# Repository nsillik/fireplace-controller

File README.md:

# Nick's Fireplace Controller Thingy

## Why did you make this?

In 2022 we bought an _old_ house. A big ol' victorian built in 1891 which had been converted to a triplex. Unfortunately during this conversion they ripped out all 8 or so original fireplaces an bricked them up. Lame. So, we though we'd put in some gas fireplaces. We did! Then we needed a way to control them, so we bought this amazing remote control system for $500 each:

Yes, that's a resistive touch screen. Yes, it really is that ugly and clunky. Yes it did somehow cost $500 dollars. No, that is not my hand. It also does all sorts of annoying things, like only allow you to adust the time by one minute, so if you want to run your fireplace for 2 hours, have fun hitting the (again, resistive) "add minute" button _one hundred and twenty times_.

I hated this, my wife ([@jensillik](https://github.com/jensillik)) hated it, so we decided to do something about it. And here it is.

## How did you make it?

Well, like every computer person of a certain age, I have a giant pile of electronics, raspberry pis, arduinos, ESP8266s, ESP32s, PICs, PIDs, and whatnot lying around that I always pretended I would do something useful with. Mostly I would make an LED blink every few seconds, or say "I'm going to build a robot" and then… make an LED blink every few seconds.

So I gathered up some of my bits and bobs – namely an ESP32, a breadboard, some resistors, a relay, and _of course_ some LEDs for blinking – and slapped them together into some configuration that I was pretty sure would actually control the fireplace's electronics. Then I wrote some firmware code in ESP-IDF that actually turns on and off the relay (_and_ blinks LEDs). I wrote an iOS app (that was ugly), then Jen made some beautiful Figma designs, and so I made the app pretty! Finally I (tried) to build the schematics and PCB layouts for eventual actual-production of hardware!

That all became the following three things:

- *Flicker*: the firmware running on an ESP32 which handles wifi networking, a custom UDP protocol for remote control, and hareware control of the relay for turning the fireplace on and off.

- *Flame*: an iOS app, written in SwiftUI, for the users (all two of us) to control the fireplaces and view their statuses.

- *Spark*: a [KiCad](https://www.kicad.org/) project with schematics, BOM, and PCB layout for eventually actually manufacturing a good looking piece of hardware instead of a breadboard shoved under the fireplace.

Read on for details of all three

### ⚡️ Flicker - ESP32 Firmware

If you're in to electronics projects and somehow haven't heard of the [ESP32](https://www.espressif.com/en/products/socs/esp32), you're missing out. What a cool little chip! It's got:

- A dual core processor!
- 520KB of RAM!
- 448KB of ROM!
- WiFi (802.11 b/g/n)!
- Bluetooth (including BLE)!
- Tons of GPIO, ADCs, DACs, SPI, I2S, I2C, and more!

And it costs something like $6 for a devevelopment board!

For this project it's probably a bit of overkill, of course, since I'm using exactly _one_ GPIO. But the WiFi is _way_ easier – and cheaper – to get up and running than screwing around with an Arduino and some sort of shield. Also I had like 10 of them in a drawer, so why not?

When programming the ESP32 you can either use the Arduino SDK that everyone knows and loves, or Expressif's [ESP-IDF](https://docs.espressif.com/projects/esp-idf/en/latest/esp32/get-started/). I've done a bunch of things (like… making LEDs blink _a lot_) in Arduino, so I decided to use ESP-IDF just for fun.

For development I used [VSCode](https://code.visualstudio.com/) and the [PlatformIO](https://platformio.org/) extension which has boards and extensions and libraries and whatnot for the ESP32.

There's really only three interesting pieces of the code:

- The communcation protocol handler
- The wifi code
- The main app that ties it all together

I won't talk much about the last two, as they're pretty much just copies of the reference implementations for each from Expressif's docs with some things hardcoded for my network, like my WPA2 key (please don't hack me).

The communications handler (in [`/flicker/src/listener.c`](/flicker/src/listener.c)) is fun, and has a good description of the custom protocol in it. Here's how it works:

`udp_server_task` is a function that you pass to [FreeRTOS's](https://www.freertos.org/index.html) [`xTaskCreate`](https://www.freertos.org/a00125.html). This creates a task which FreeRTOS will schedule (somehow! I've not dug too deep into the guts).

This `udp_server_task` then binds a UDP (`SOCK_DGRAM`) listener on port `42069` (sorry, sorry, I'm trying to delete it), and then just busyloops listening for any messages. "Messages" here are just a super-simple protocol:

```
// 
// Command structure:
// Clients send commands in the following format:
// 0000 0000 0000 0000
// ^^|---------------|
// ||        | 
// ||        \--------> For command `10` The amount of time, in seconds to turn on for (for turn on command). Otherwise unused (zero is recommended)
// ||  
// \\-----------------> The command to send `00` for turn off, `01` for status, `10` for turn on
// 
// Server always replies with its status, either:
//  - `0000 0000 0000 0000` for off
//  - `10XX XXXX XXXX XXXX` for on, with the Xs being the time remaining in seconds
```

Basically a client can do three things:
- Send `0x4000`, requesting the status
- Send `0x8000 | (0x3FFF & 0xXXXX)` to turn the fireplace on for `XXXX` seconds (well, with the top two bits masked off)
- Send `0x0000` to turn the fireplace off.

When the server recieves these from the clients it updates it's current status which is just a shared (kinda gross, I know) `uint16_t`, and then sends the current (or updated) status back to the client.

There's another FreeRTOS task in `listener.c` called `statusLoop` which, every second, takes a look at the current status, and makes sure that the hardware is doing the right thing. That is:

- If the current status is `on`, decrement the time remaining by one second, and if it's now zero set the status to `off`.
- If the current status if `on`, and there's time remaining, make sure the `RELAY_PIN` is set to on. This closes the relay and the fireplace turns – or stays – on fire.
- If the current status is `off`, open the relay thereby turning the fireplace off, extinguishing the flame.

That's about it!

You'll see how this is all hooked up in [`flicker/src/main.c`](/flicker/src/main.c), which only does three things:

1. Sets up the networking (lines 12-21)
2. Schedules the two tasks above (lines 22 and 23).

That's it! Now we're ready for a client to actually start talking to it.

### 🔥 Flame - iOS App

And this is that client. An iOS app, written in SwiftUI, designed by the wonderul Jen Sillik. Here's the design:

There's only a few big pieces here:

- A `FireplaceService` which handles communication with the `Flicker` controller, as well as a test version for using in Xcode Previews.
- A `MainScreen` which is 100% of the UI and logic.
- A couple views like the custom `Picker`, the `GlassButtonStyle`, and the pretty `BackgroundView`.

#### `FireplaceService`

The [`FireplaceService`](/flame/flame/Services/FireplaceService.swift) is really the heart of the application. It's a reasonably simple protocol to conform to:

```swift
protocol FireplaceService: ObservableObject {
  var fireplaces: [Fireplace] { get }
  func turnOnFireplace(_ fireplace: Fireplace, minutes: UInt16) async -> Fireplace
  func turnOffFireplace(_ fireplace: Fireplace) async -> Fireplace
}
```

You can get a list of fireplaces. You can turn on the fireplace. You can turn off the fireplace. Not really much else to do! The `LiveFireplaceService` implements the real-for-real version of this which connects to the fireplaces in my house. The IP addresses are hardcoded, since I have my DHCP server always assign the same IP to the devices (because I'm lazy and didn't feel like doing mDNS in ESP-IDF, maybe some day).

Basically when this guy is `init`-ed it connects to all of the hardcoded fireplaces, gets their status, and then sets a timer to check on the status of the fireplaces every 20 seconds (I had it doing it every 200ms, but that was silly!). This is all done using the built in [`NWConnection`](https://developer.apple.com/documentation/network/nwconnection) which is pretty straightforward.

The connecting happens in the `connectTo` function which is pretty boring boilerplate, so I'm not going to say anymore about that.

The `requestStatus(fireplace:, connection:)` method sends the status message (`0x4000`), and that's it. Messages recieved _from_ the `Flicker` controllers are handled by the `receive(fireplace:, connection:)` method, and literally just update our internal list of fireplaces.

The `turnOnFireplace(_ fireplace: Fireplace, minutes: UInt16)` and `turnOffFireplace(_ fireplace:)` methods just send the corresponding commands to the specified `Fireplace`. Easy-peasy.

Alllll of this is then injected into the SwiftUI Environment as an `EnvironmentObject` as a lazy-man's form of dependency injection.

#### `MainScreen`

The [`MainScreen`](/flame/flame/MainScreen.swift) is the only screen in the app (if only every app was just a single screen…), it's got a `FireplaceService` that it gets like so:
```swift
@EnvironmentObject var fireplaceService
```

And it keeps its state updated based on the currently selected fireplace (and that fireplaces current state). And then (depending on the current state), it has buttons to turn on, turn off, and adjust the time of the current selected fireplace.

#### Some rando views

There's a couple views in here too, but they're not to interesting. Quickly:

- [`Picker`](/flame/flame/Views/Picker.swift): is just a custom little picker view to match Jen's designs. You give it `options`, and it has a `@Binding` for the currently selected option. Neato!
- [`GlassButton`](/flame/flame/Views/GlassButton.swift): is a custom `ButtonStyle` for making the glassy looking buttons. There's actually a little bug here, but I haven't got a chance to sit down w/ my fantastic designer to work them out. It's good enough for now!
- [`BackgroundView`](/flame/flame/Views/BackgroundView.swift): is the pretty view that's the background of the whole app. It's a steely blue-gray color when the fireplace is off, and a warm orange-yellow color when the fireplace is on. Eventually I'm going to make this pretty and feel more alive.

#### That's it

Yeah, really. That's the whole app

### ✨ Spark - Hardware Design

As an added challenge I am trying to actually get the hardware manufactured. I haven't done it yet, and it'll probably be a disaster, but you can take a look at my attempts!

I'm using [KiCad](https://www.kicad.org/), a free and open-source EDA tool. To start, I needed to build a schematic. I used the [ESP32-DevKitC V4](https://docs.espressif.com/projects/esp-idf/en/latest/esp32/hw-reference/esp32/get-started-devkitc.html) as my starting guide. This includes:

- The ESP32
- A usb connector
- A [`CP2102N`](https://www.silabs.com/documents/public/data-sheets/cp2102n-datasheet.pdf) USB-to-UART controller for serial access
- An [`AS1117`](http://www.advanced-monolithic.com/pdf/ds1117.pdf) voltage regulator for going from USBs 5v to the 3.3v that the ESP32 runs on.
- A few buttons, transistors, caps, resistors, diodes, and – of course – blinking LEDs.

On top of that I added a [SRD-03VDC-SL-C](https://pdf1.alldatasheet.com/datasheet-pdf/view/1132027/SONGLERELAY/SRD-03VDC-SL-C.html) relay for actually controlling the fireplace. Oh yeah, and there's some transistors and resistors and diodes around the relay so that it… relays correctly? IDK 🤷‍♀️

I laid that all out in the schematic editor – mostly according to datasheets, example circuits, and with the help of a few buddies – and it ended up looking like this:

After that I had to put together the BOM and footprints (although, I'm pretty sure I got some wrong, will be doing like 10 more reviews before ordering):

And then, for the hard part, laying out a PCB. Okay, I'm terrible at this, and this was like my 12th attempt. I got everything hooked up, but it's still _really ugly_. It looks like this:

And, one day, when I send it to [JLCPCB](https://jlcpcb.com/) for assembly, it'll end up looking something like this:

### ✍️ What's left to do?

Does it work? Yes! Am I done? Probably not. There's a few more things I'd like to do, most of which I mentioned above:

- Prettier animations in the app! Especially making the background feel a bit more alive.
- Fixing the `GlassButtonStyle` to not be kinda-wrong at times
- Reviewing and checking the schematics (and trying to force friends to do the same) to spot any bugs.
- Probably re-laying out the PCB another 15 or so times until I'm happy with it. It's a bit bigger than I'd like it to be. Maybe I can find a smaller relay?

### 🧨 Is this safe?

God, I hope so 😬

### That's it

If you read this far, sorry! Hope you learned something, even if that something was "don't hire @nsillik for electrical engineering!".

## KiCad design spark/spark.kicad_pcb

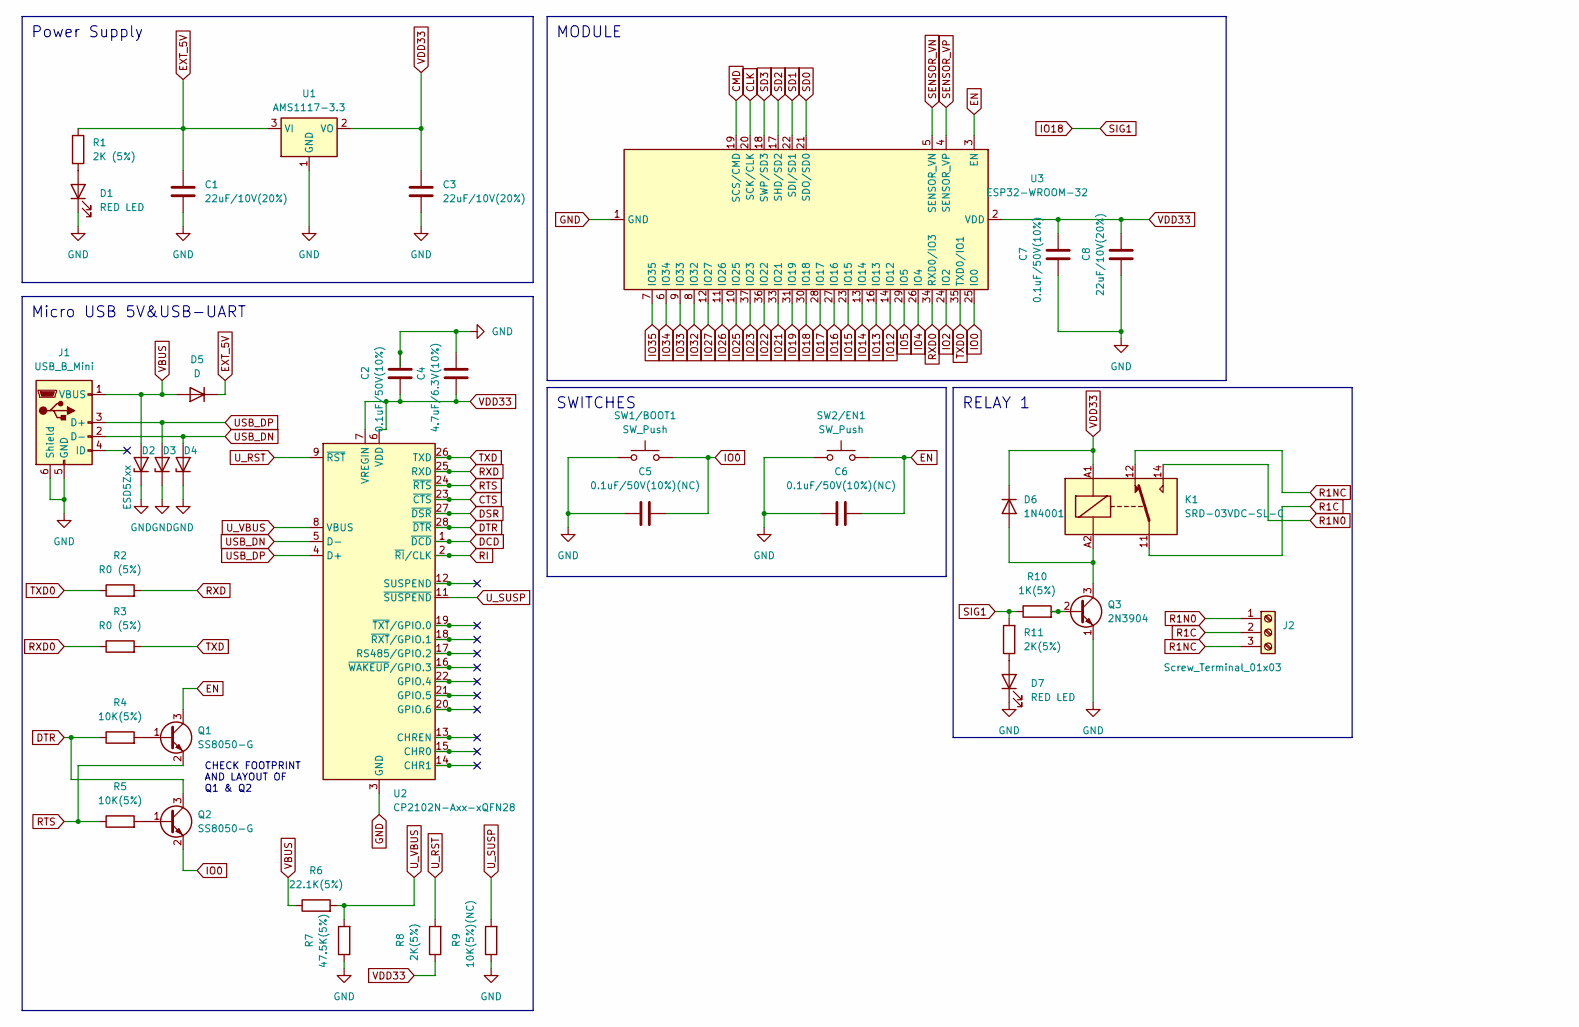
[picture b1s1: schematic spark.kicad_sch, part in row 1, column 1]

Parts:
C1, C3, C8: 22uF/10V(20%); C_0402_1005Metric
C2, C7: 0.1uF/50V(10%); C_0402_1005Metric
C4: 4.7uF/6.3V(10%); C_0402_1005Metric
C5, C6: 0.1uF/50V(10%)(NC); C_0402_1005Metric
D1, D7: RED LED; LED_0805_2012Metric_Pad1.15x1.40mm_HandSolder
D2, D3, D4: ESD5Zxx; D_SOD-523
D5: D; D_0402_1005Metric
D6: 1N4001; D_DO-41_SOD81_P10.16mm_Horizontal
J1: USB_B_Mini; USB_Mini-B_Lumberg_2486_01_Horizontal
J2: Screw_Terminal_01x03; TerminalBlock_TE_282834-3_1x03_P2.54mm_Horizontal
K1: SRD-03VDC-SL-C; Relay_SPDT_SANYOU_SRD_Series_Form_C_WithA
Q1, Q2: SS8050-G; SOT-23
Q3: 2N3904; TSOT-23
R1: 2K (5%); R_0402_1005Metric
R2, R3: R0 (5%); R_0402_1005Metric
R4, R5: 10K(5%); R_0402_1005Metric
R6: 22.1K(5%); R_0402_1005Metric
R7: 47.5K(5%); D_SOD-523
R8: 2K(5%); C_0402_1005Metric
R9: 10K(5%)(NC); R_0402_1005Metric
R10: 1K(5%); R_0402_1005Metric
R11: 2K(5%); R_0402_1005Metric
SW1/BOOT1, SW2/EN1: SW_Push; SW_Push_1P1T_NO_CK_KSC7xxJ
U1: AMS1117-3.3; SOT-223-3_TabPin2
U2: CP2102N-Axx-xQFN28; QFN-28-1EP_5x5mm_P0.5mm_EP3.35x3.35mm
U3: ESP32-WROOM-32

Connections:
CLK: U3.20 (SCK/CLK)
CMD: U3.19 (SCS/CMD)
CTS: U2.23 (~CTS)
DCD: U2.1 (~DCD)
DSR: U2.27 (~DSR)
DTR: Q2.3 (C), R4.1, U2.28 (~DTR)
EN: C6.2, Q1.3 (C), SW2/EN1.2, U3.3 (EN)
EXT_5V: C1.1, D5.1 (K), R1.1, U1.3 (VI)
GND: C1.2, C2.1, C3.2, C4.1, C5.1, C6.1, C7.2, C8.2, D1.1 (K), D2.1 (K), D3.1 (K), D4.1 (K), D7.1 (K), J1.5 (GND), J1.6 (Shield), Q3.1 (E), R7.1, R9.1, SW1/BOOT1.1, SW2/EN1.1, U1.1 (GND), U2.3 (GND), U2.29 (GND), U3.1 (GND), U3.15 (GND), U3.38 (GND), U3.39 (GND); also elsewhere on the board
IO0: C5.2, Q2.2 (E), SW1/BOOT1.2, U3.25 (IO0)
IO2: U3.24 (IO2)
IO4: U3.26 (IO4)
IO5: U3.29 (IO5)
IO12: U3.14 (IO12)
IO13: U3.16 (IO13)
IO14: U3.13 (IO14)
IO15: U3.23 (IO15)
IO16: U3.27 (IO16)
IO17: U3.28 (IO17)
IO18: R10.1, R11.2, U3.30 (IO18)
IO19: U3.31 (IO19)
IO21: U3.33 (IO21)
IO22: U3.36 (IO22)
IO23: U3.37 (IO23)
IO25: U3.10 (IO25)
IO26: U3.11 (IO26)
IO27: U3.12 (IO27)
IO32: U3.8 (IO32)
IO33: U3.9 (IO33)
IO34: U3.6 (IO34)
IO35: U3.7 (IO35)
unnamed: D1.2 (A), R1.2
unnamed: D6.2 (A), K1.A2, Q3.3 (C)
unnamed: D7.2 (A), R11.1
unnamed: Q1.1 (B), R4.2
unnamed: Q2.1 (B), R5.2
unnamed: Q3.2 (B), R10.2
R1C: J2.2, K1.11
R1N0: J2.1, K1.14
R1NC: J2.3, K1.12
RI: U2.2 (~RI/CLK)
RTS: Q1.2 (E), R5.1, U2.24 (~RTS)
RXD: R2.2, U2.25 (RXD)
RXD0: R3.1, U3.34 (RXD0/IO3)
SD0: U3.21 (SDO/SD0)
SD1: U3.22 (SDI/SD1)
SD2: U3.17 (SHD/SD2)
SD3: U3.18 (SWP/SD3)
SENSOR_VN: U3.5 (SENSOR_VN)
SENSOR_VP: U3.4 (SENSOR_VP)
TXD: R3.2, U2.26 (TXD)
TXD0: R2.1, U3.35 (TXD0/IO1)
USB_DN: D4.2 (A), J1.2 (D-), U2.5 (D-)
USB_DP: D3.2 (A), J1.3 (D+), U2.4 (D+)
U_RST: R8.2, U2.9 (~RST)
U_SUSP: R9.2, U2.11 (~SUSPEND)
U_VBUS: R6.2, R7.2, U2.8 (VBUS)
VBUS: D2.2 (A), D5.2 (A), J1.1 (VBUS), R6.1; also elsewhere on the board
VDD33: C2.2, C3.1, C4.2, C7.1, C8.1, D6.1 (K), K1.A1, R8.1, U1.2 (VO), U2.6 (VDD), U2.7 (VREGIN), U3.2 (VDD)

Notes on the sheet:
RELAY 1
SWITCHES
Power Supply
Micro USB 5V&USB-UART
MODULE
CHECK FOOTPRINT AND LAYOUT OF Q1 & Q2

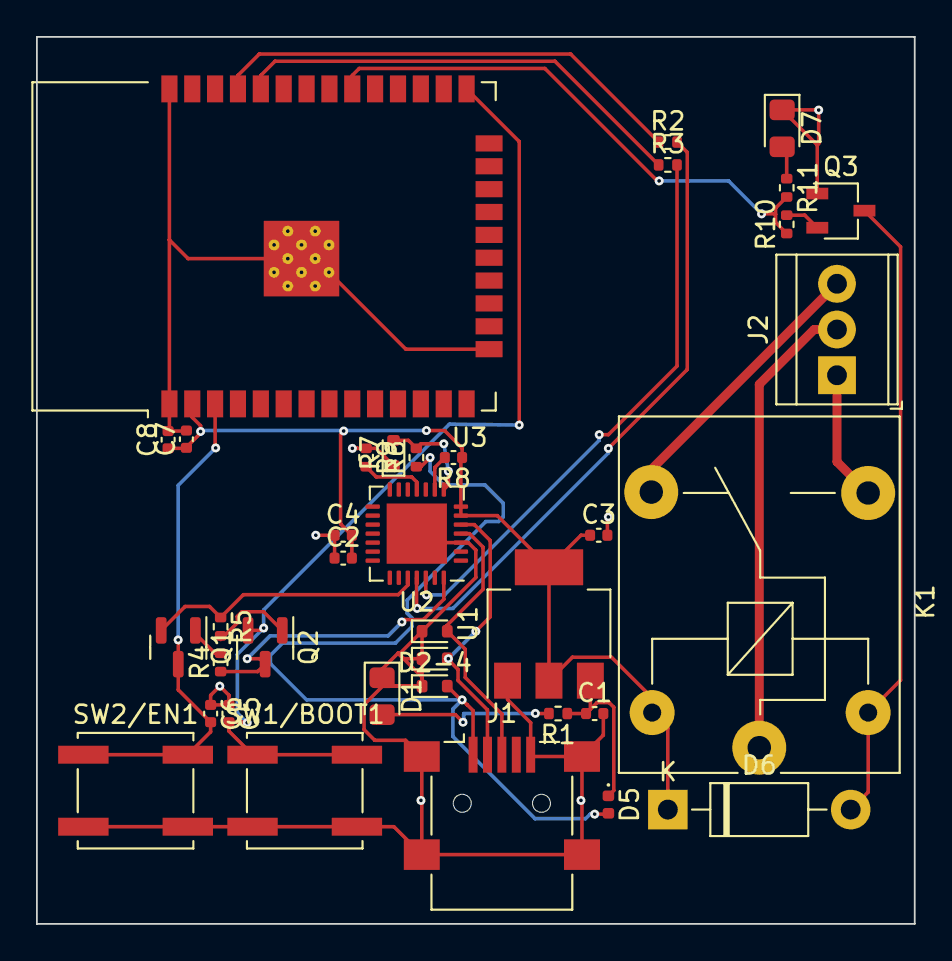
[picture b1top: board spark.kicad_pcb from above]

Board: 2 copper layers, 48.8 x 49.3 mm, 37 parts (0 on the bottom side), 27 nets.

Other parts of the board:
D2-4: ESD5Zxx; D_SOD-523

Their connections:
GND: D2-4.1 (K); also elsewhere on the board
VBUS: D2-4.2 (A); also elsewhere on the board

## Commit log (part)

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2023-01-08 start
2023-01-08 wifi working, esp32 setup done
2023-02-05 working mostly
2023-02-05 get rid of useless led blink
2023-02-05 GPL (#1)
2023-10-04 add initial, empty, KiCAD project
2023-10-04 Remove unneeded constant
2023-10-04 remove user data
2023-10-05 Pretty Views! Cleanup old code.
2023-10-05 Fix service, get main UI working
2023-10-06 Fix safe area issue with picker, add start of GlassButton
2023-10-06 Animations from Jen's feedback
2023-10-08 Add basic esp32 board (and some bonus design fixes to app)
2023-10-08 whoops, forgot the switches
2023-10-11 Working PCB #1
2023-10-11 fix all design rules issues
2023-10-13 Another checkpoint, going to do layout again for funsies
2023-10-16 Add readme
2024-10-13 format, default to 30, gitignore, texting
2026-03-09 Migrate to mise & tuist
2026-03-14 More tuist, more TCA
